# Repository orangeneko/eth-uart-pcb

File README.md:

## About
Simple Ethernet TCP/IP to Serial UART x4 converter

## PCB

## Hardware
* Cortex M4 STM32F407VETx
* Ethernet PHY DP83848

## Software
Firmware based on FreeRTOS and lwIP

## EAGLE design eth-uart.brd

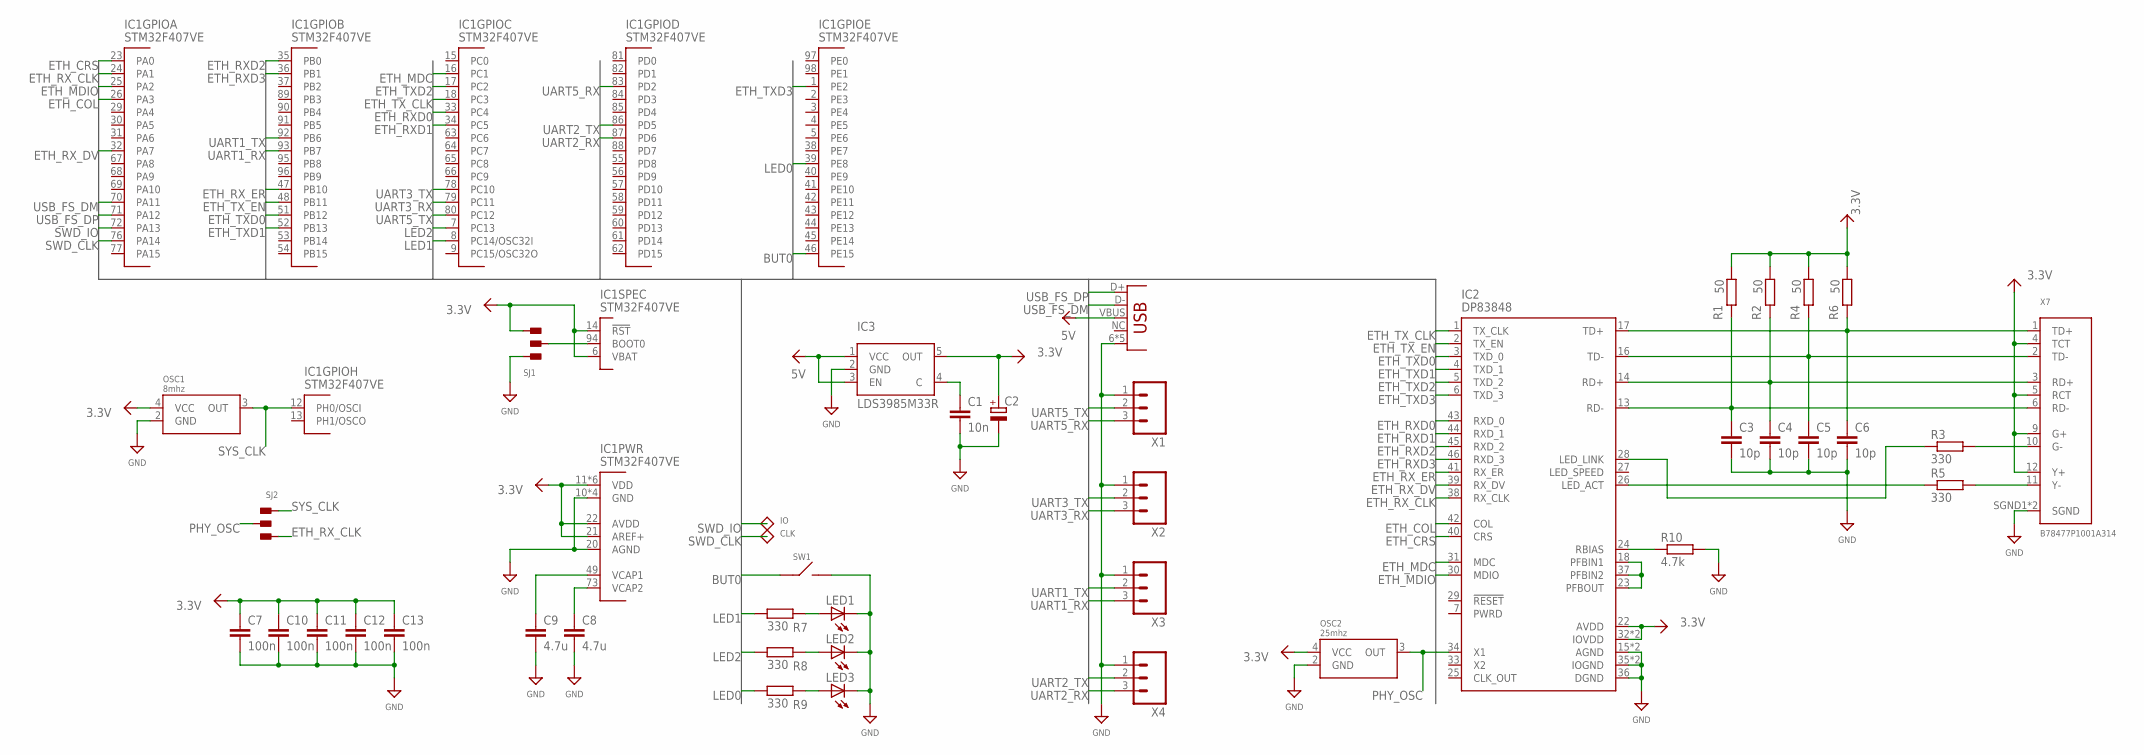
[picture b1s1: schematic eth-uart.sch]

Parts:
C1: 10n; R0402
C2: CPOL-EUSMCA; SMC_A
C3, C4, C5, C6: 10p; R0402
C7, C10, C11, C12, C13: 100n; R0402
C8, C9: 4.7u; R0603
IC1: STM32F407VE; LQFP100
IC2: DP83848; LQFP-48
IC3: LDS3985M33R; SOT23-5
LED1, LED2, LED3: LED0603
OSC1: 8mhz; 3225
OSC2: 25mhz; 3225
R1, R2, R4, R6: 50; R0402
R3, R5, R7, R8, R9: 330; R0402
R10: 4.7k; R0402
SJ1, SJ2: SJ3
SW1: BUT; SONY_ERRICSON_SW
TP1: IO; TP06R
TP2: CLK; TP06R
X1, X2, X3, X4: M03; 1X03
X5: USBMICRO_B; USB_MICROB
X7: B78477P1001A314; HR911105A

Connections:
3.3V: C2.+, C7.1, C10.1, C11.1, C12.1, C13.1, IC1.6 (VBAT), IC1.11 (VDD), IC1.14 (!RST), IC1.19 (VDD), IC1.21 (AREF+), IC1.22 (AVDD), IC1.28 (VDD), IC1.50 (VDD), IC1.75 (VDD), IC1.100 (VDD), IC2.22 (AVDD), IC2.32 (IOVDD), IC2.48 (IOVDD), IC3.5 (OUT), OSC1.4 (VCC), OSC2.4 (VCC), R1.1, R2.1, R4.1, R6.1, SJ1.3, X7.4 (TCT), X7.5 (RCT), X7.9 (G+), X7.12 (Y+)
5V: IC3.1 (VCC), IC3.3 (EN), X5.VBUS
BOOT0: IC1.94 (BOOT0), SJ1.2
BUT0: IC1.46 (PE15), SW1.1
ETH_COL: IC1.26 (PA3), IC2.42 (COL)
ETH_CRS: IC1.23 (PA0), IC2.40 (CRS)
ETH_MDC: IC1.16 (PC1), IC2.31 (MDC)
ETH_MDIO: IC1.25 (PA2), IC2.30 (MDIO)
ETH_RXD0: IC1.33 (PC4), IC2.43 (RXD_0)
ETH_RXD1: IC1.34 (PC5), IC2.44 (RXD_1)
ETH_RXD2: IC1.35 (PB0), IC2.45 (RXD_2)
ETH_RXD3: IC1.36 (PB1), IC2.46 (RXD_3)
ETH_RX_CLK: IC1.24 (PA1), IC2.38 (RX_CLK), SJ2.3
ETH_RX_DV: IC1.32 (PA7), IC2.39 (RX_DV)
ETH_RX_ER: IC1.47 (PB10), IC2.41 (RX_ER)
ETH_TXD0: IC1.51 (PB12), IC2.3 (TXD_0)
ETH_TXD1: IC1.52 (PB13), IC2.4 (TXD_1)
ETH_TXD2: IC1.17 (PC2), IC2.5 (TXD_2)
ETH_TXD3: IC1.1 (PE2), IC2.6 (TXD_3)
ETH_TX_CLK: IC1.18 (PC3), IC2.1 (TX_CLK)
ETH_TX_EN: IC1.48 (PB11), IC2.2 (TX_EN)
GND: C1.2, C2.-, C3.2, C4.2, C5.2, C6.2, C7.2, C8.2, C9.2, C10.2, C11.2, C12.2, C13.2, IC1.10 (GND), IC1.20 (AGND), IC1.27 (GND), IC1.74 (GND), IC1.99 (GND), IC2.15 (AGND), IC2.19 (AGND), IC2.35 (IOGND), IC2.36 (DGND), IC2.47 (IOGND), IC3.2 (GND), LED1.C, LED2.C, LED3.C, OSC1.2 (GND), OSC2.2 (GND), R10.2, SJ1.1, SW1.2, X1.1, X2.1, X3.1, X4.1, X5.6 (GND), X5.7 (GND), X5.8 (GND), X5.9 (GND), X5.GND, X7.SGND1 (SGND), X7.SGND2 (SGND)
LED0: IC1.39 (PE8), R9.1
LED1: IC1.8 (PC14/OSC32I), R7.1
LED2: IC1.7 (PC13), R8.1
LED_ACT: IC2.26 (LED_ACT), R5.1
LED_G: R3.2, X7.10 (G-)
LED_LINK: IC2.28 (LED_LINK), R3.1
LED_Y: R5.2, X7.11 (Y-)
unnamed: IC2.18 (PFBIN1), IC2.23 (PFBOUT), IC2.37 (PFBIN2)
unnamed: C1.1, IC3.4 (C)
unnamed: LED1.A, R7.2
unnamed: LED2.A, R8.2
unnamed: LED3.A, R9.2
unnamed: IC2.24 (RBIAS), R10.1
unnamed: C8.1, IC1.73 (VCAP2)
unnamed: C9.1, IC1.49 (VCAP1)
PHY_OSC: IC2.34 (X1), OSC2.3 (OUT), SJ2.2
RXDM: C3.1, IC2.13 (RD-), R1.2, X7.6 (RD-)
RXDP: C4.1, IC2.14 (RD+), R2.2, X7.3 (RD+)
SWD_CLK: IC1.76 (PA14), TP2.TP
SWD_IO: IC1.72 (PA13), TP1.TP
SYS_CLK: IC1.12 (PH0/OSCI), OSC1.3 (OUT), SJ2.1
TXDM: C5.1, IC2.16 (TD-), R4.2, X7.2 (TD-)
TXDP: C6.1, IC2.17 (TD+), R6.2, X7.1 (TD+)
UART1_RX: IC1.93 (PB7), X3.3
UART1_TX: IC1.92 (PB6), X3.2
UART2_RX: IC1.87 (PD6), X4.3
UART2_TX: IC1.86 (PD5), X4.2
UART3_RX: IC1.79 (PC11), X2.3
UART3_TX: IC1.78 (PC10), X2.2
UART5_RX: IC1.83 (PD2), X1.3
UART5_TX: IC1.80 (PC12), X1.2
USB_FS_DM: IC1.70 (PA11), X5.D-
USB_FS_DP: IC1.71 (PA12), X5.D+

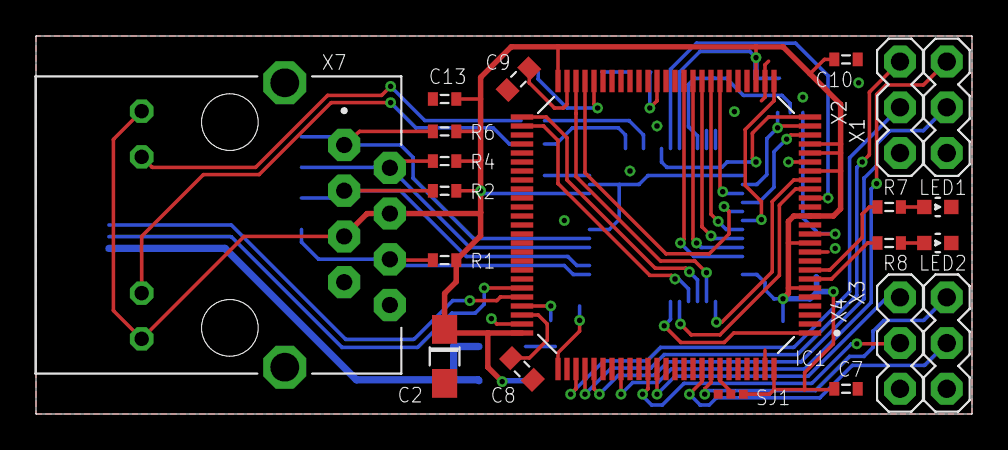
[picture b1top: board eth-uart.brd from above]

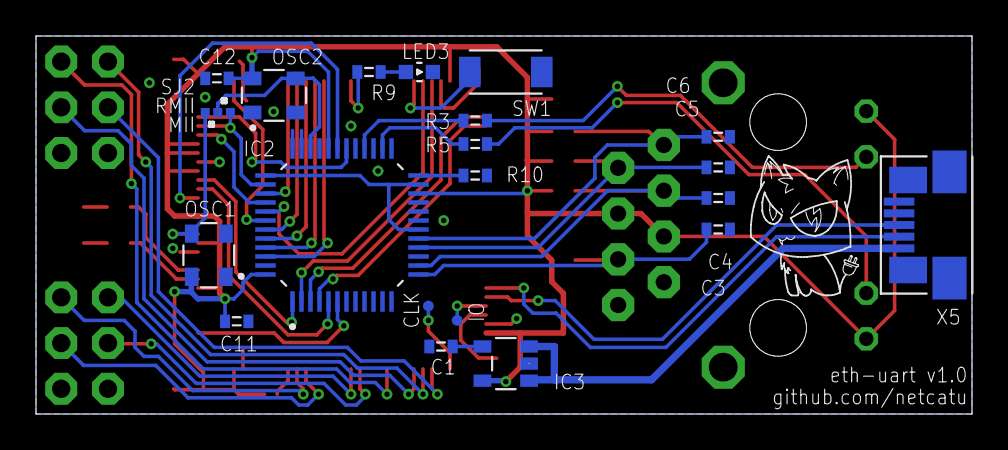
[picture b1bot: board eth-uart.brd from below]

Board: 2 copper layers, 52.0 x 21.0 mm, 43 parts (22 on the bottom side), 55 nets.

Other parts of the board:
U$1: LOGO2

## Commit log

2018-07-03 first pcb draft
2018-07-03 boot0 on solidjump
2018-07-03 changed eth socket to HR911105A
2018-07-06 added solid jumper for RMII/MII clock selecting
2018-07-25 first release, update doc & gerber
